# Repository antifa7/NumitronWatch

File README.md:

# NumitronWatch
A work in progress. ATMega328P controlled IV-16 tube two digit watch

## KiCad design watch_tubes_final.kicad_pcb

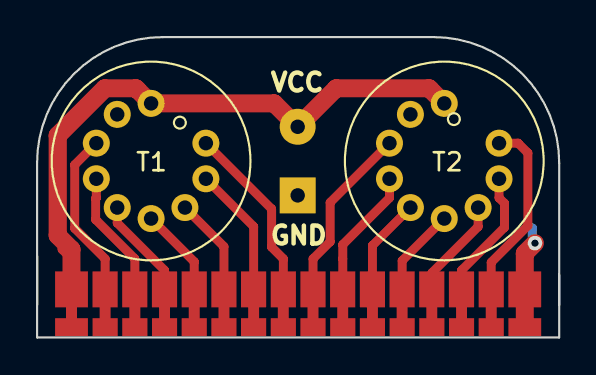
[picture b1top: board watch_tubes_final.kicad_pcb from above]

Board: 2 copper layers, 29.0 x 16.7 mm, 4 parts (0 on the bottom side), 16 nets.

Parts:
CONN2: wire conn; SolderWirePad_1x02_P3.81mm_Drill0.8mm
GND: PCBMOUNT-20SECOND; numitronWatchPCBMountTubev1
T1, T2: IV-16

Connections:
/T1D3: GND.1, T1.3
/T1D4: GND.2, T1.4
/T1D5: GND.3, T1.5
/T1D6: GND.4, T1.6
/T1D7: GND.5, T1.7
/T1D8: GND.6, T1.8
/T1D9: GND.7, T1.9
/T2D3: GND.8, T2.3
/T2D4: GND.9, T2.4
/T2D5: GND.10, T2.5
/T2D6: GND.11, T2.6
/T2D7: GND.12, T2.7
/T2D8: GND.13, T2.8
/T2D9: GND.14, T2.9
GND: CONN2.1, GND.P1
VCC: CONN2.2, GND.P2, T1.1, T2.1

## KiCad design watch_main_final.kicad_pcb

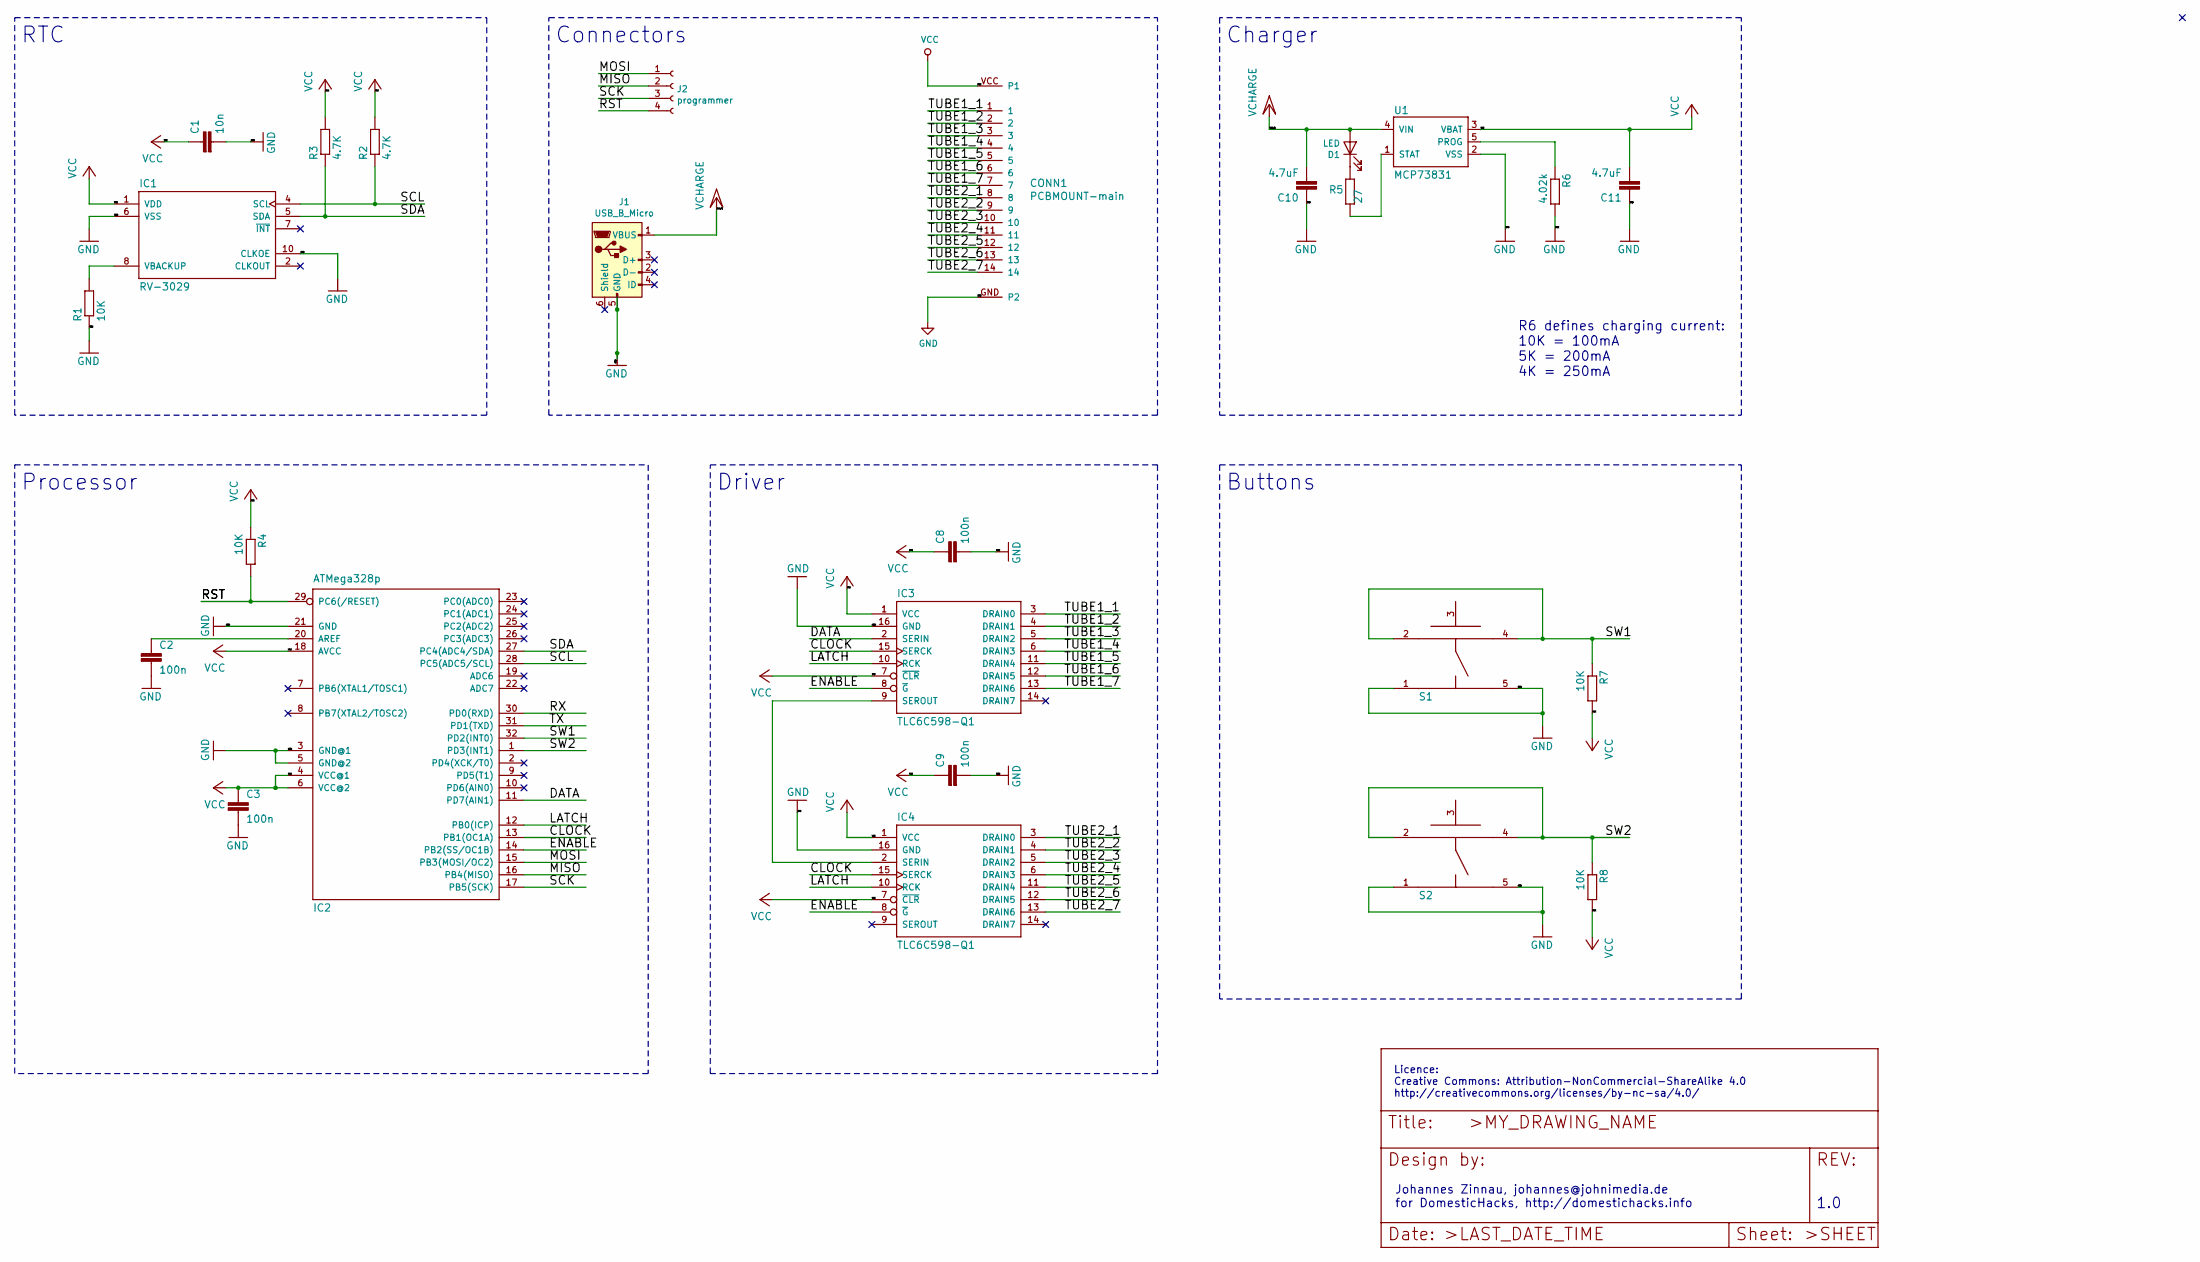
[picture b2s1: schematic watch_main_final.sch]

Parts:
C1: 10n; C0603; LCSC C57112
C2, C3, C8, C9: 100n; C0603; LCSC C14663
C10, C11: 4.7uF; C0603; LCSC C53987
CONN1: PCBMOUNT-main; numitronWatchPCBMountTube
D1: LED; LED_0805_2012Metric_Pad1.15x1.40mm_HandSolder; LCSC C2293
IC1: RV-3029; RV-3029-C2
IC2: ATMega328p; TQFP-32_7x7mm_P0.8mm; LCSC C14877
IC3, IC4: TLC6C598-Q1; TSSOP-16; LCSC C132050
J1: USB_B_Micro; USB_MicroB
J2: programmer; PinHeader_1x04_P2.54mm_Vertical
R1, R4, R7, R8: 10K; R0603; LCSC C25804
R2, R3: 4.7K; R0603; LCSC C23162
R5: 27; R0603; LCSC C25190
R6: 4.02k; R0603
S1, S2: KMSXXXG; C&K-KMS-SWITCH
U1: MCP73831; SOT23-5; LCSC C14879

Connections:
/CLOCK: IC2.13 (PB1(OC1A)), IC3.15 (SERCK), IC4.15 (SERCK)
/DATA: IC2.11 (PD7(AIN1)), IC3.2 (SERIN)
/ENABLE: IC2.14 (PB2(SS/OC1B)), IC3.8 (~G), IC4.8 (~G)
/LATCH: IC2.12 (PB0(ICP)), IC3.10 (RCK), IC4.10 (RCK)
/MISO: IC2.16 (PB4(MISO)), J2.2
/MOSI: IC2.15 (PB3(MOSI/OC2)), J2.1
/RST: IC2.29 (PC6(/RESET)), J2.4, R4.2
/RX: IC2.30 (PD0(RXD))
/SCK: IC2.17 (PB5(SCK)), J2.3
/SCL: IC1.4 (SCL), IC2.28 (PC5(ADC5/SCL)), R2.1
/SDA: IC1.5 (SDA), IC2.27 (PC4(ADC4/SDA)), R3.1
/SW1: IC2.32 (PD2(INT0)), R7.1, S1.2, S1.4
/SW2: IC2.1 (PD3(INT1)), R8.1, S2.2, S2.4
/TUBE1_1: CONN1.1, IC3.3 (DRAIN0)
/TUBE1_2: CONN1.2, IC3.4 (DRAIN1)
/TUBE1_3: CONN1.3, IC3.5 (DRAIN2)
/TUBE1_4: CONN1.4, IC3.6 (DRAIN3)
/TUBE1_5: CONN1.5, IC3.11 (DRAIN4)
/TUBE1_6: CONN1.6, IC3.12 (DRAIN5)
/TUBE1_7: CONN1.7, IC3.13 (DRAIN6)
/TUBE2_1: CONN1.8, IC4.3 (DRAIN0)
/TUBE2_2: CONN1.9, IC4.4 (DRAIN1)
/TUBE2_3: CONN1.10, IC4.5 (DRAIN2)
/TUBE2_4: CONN1.11, IC4.6 (DRAIN3)
/TUBE2_5: CONN1.12, IC4.11 (DRAIN4)
/TUBE2_6: CONN1.13, IC4.12 (DRAIN5)
/TUBE2_7: CONN1.14, IC4.13 (DRAIN6)
/TX: IC2.31 (PD1(TXD))
GND: C1.2, C2.2, C3.2, C8.2, C9.2, C10.1, C11.1, CONN1.GND (P2), IC1.6 (VSS), IC1.10 (CLKOE), IC2.3 (GND@1), IC2.5 (GND@2), IC2.21 (GND), IC3.16 (GND), IC4.16 (GND), J1.5 (GND), R1.1, R6.2, S1.1, S1.5, S2.1, S2.5, U1.2 (VSS)
unnamed: C2.1, IC2.20 (AREF)
unnamed: D1.1 (K), R5.2
unnamed: IC1.8 (VBACKUP), R1.2
unnamed: IC3.9 (SEROUT), IC4.2 (SERIN)
unnamed: R5.1, U1.1 (STAT)
unnamed: R6.1, U1.5 (PROG)
VCC: C1.1, C3.1, C8.1, C9.1, C11.2, CONN1.VCC (P1), IC1.1 (VDD), IC2.4 (VCC@1), IC2.6 (VCC@2), IC2.18 (AVCC), IC3.1 (VCC), IC3.7 (~CLR), IC4.1 (VCC), IC4.7 (~CLR), R2.2, R3.2, R4.1, R7.2, R8.2, U1.3 (VBAT)
VCC/2: C10.2, D1.2 (A), J1.1 (VBUS), U1.4 (VIN)

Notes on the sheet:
RTC
Processor
Driver
Connectors
R6 defines charging current: 10K = 100mA 5K = 200mA 4K = 250mA
Charger
Buttons
Licence: Creative Commons: Attribution-NonCommercial-ShareAlike 4.0 http://creativecommons.org/licenses/by-nc-sa/4.0/
Johannes Zinnau, johannes@johnimedia.de for DomesticHacks, http://domestichacks.info
1.0

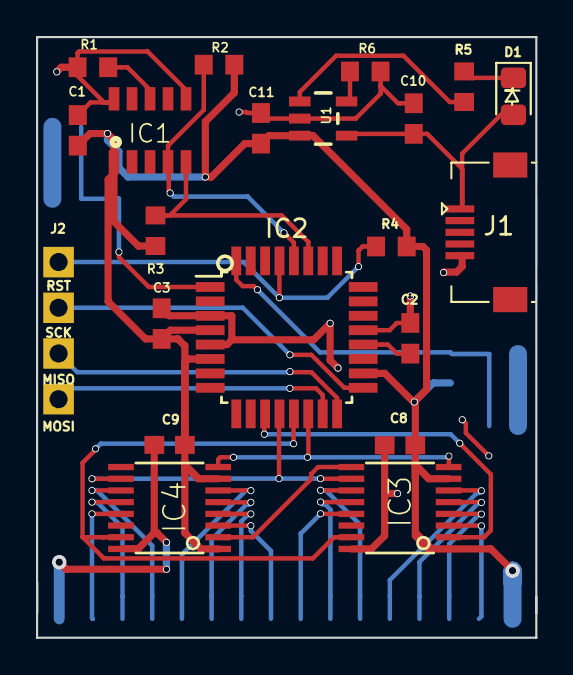
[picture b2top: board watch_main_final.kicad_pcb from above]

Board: 2 copper layers, 27.7 x 33.4 mm, 26 parts (0 on the bottom side), 35 nets.
